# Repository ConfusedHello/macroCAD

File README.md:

# MacroCAD
My own macropad made for CAD! Made for Hackclub's Highway/Hackpad event.

</img>

For this macropad, there is a function row at the bottom to switch "layers", ie. extra buttons!!

## The PCB
The PCB was designed entirely in KiCad. Here's an image of the schematic.

And an image of the PCB!

</img>

## The Case
First time using Fusion360! Went pretty well actually. Here's what we went with.

Started off by deciding on some dimensions

And moved onto creating a sketch

Then a bit more work later, the final case

Final case design (render coming soon!)

## Bill of materials
| Component                                 | Quantity | Aliexpress |
|-------------------------------------------|----------|------------|
| 2L PCB (JLCPCB with cheap shipping)       | 1        | $3.49      |
| SMD Seeed Studio XIAO RP2040              | 1        | $5.64      |
| Gateron Milky Yellows Cherry MX Switches  | 10       | ~$3.86     |
| CherryMX 1.00u Kailh Sockets              | 10       | $2.89      |
| 1N4148W Diodes (SOD-123)                  | 10       | $1.09      |
| Brass M2 Screws (approx 5mm)              | 10       | $0.97      |
| M2 Heat inserts (approx 3mm)              | 10       | $0.97      |

## Acknowledgements
- Matteo Spinelli's [Anatomy of a keyboard](https://matt3o.com/anatomy-of-a-keyboard/) for the plate thickness and hole dimensions
- MX Cherry switches footprint from [daprice/keyswitches.pretty](https://github.com/daprice/keyswitches.pretty)

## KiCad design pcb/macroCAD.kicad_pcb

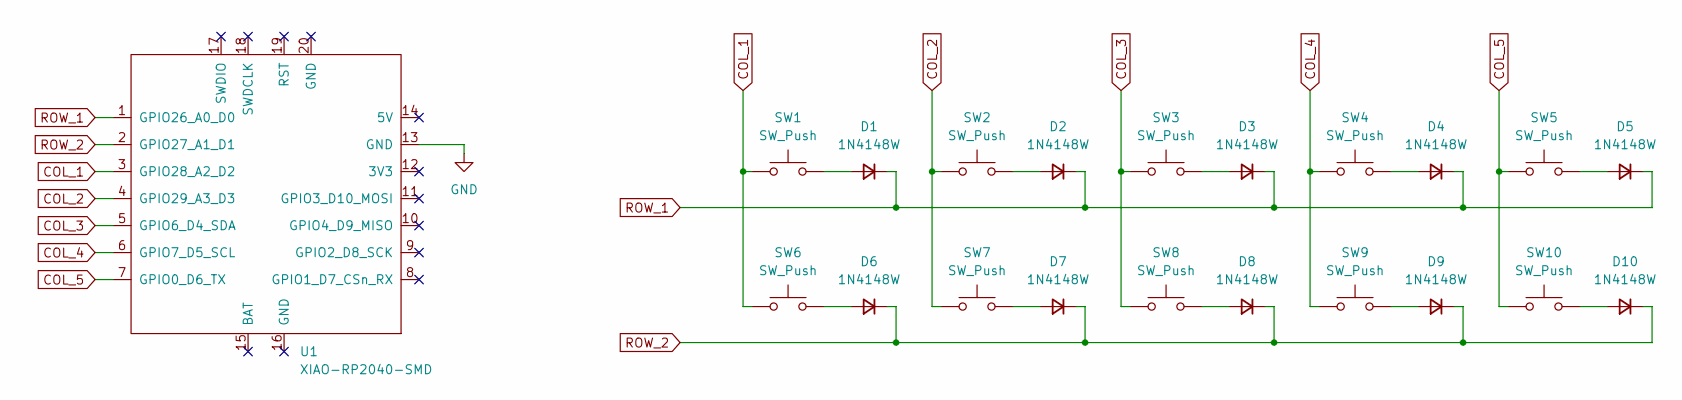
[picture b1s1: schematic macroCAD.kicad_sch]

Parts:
D1, D2, D3, D4, D5, D6, D7, D8, D9, D10: 1N4148W; D_SOD-123
SW1, SW2, SW3, SW4, SW5, SW6, SW7, SW8, SW9, SW10: SW_Push; Kailh_socket_MX
U1: XIAO-RP2040-SMD; XIAO_rp2040_SMD

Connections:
COL_1: SW1.1, SW6.1, U1.3 (GPIO28_A2_D2)
COL_2: SW2.1, SW7.1, U1.4 (GPIO29_A3_D3)
COL_3: SW3.1, SW8.1, U1.5 (GPIO6_D4_SDA)
COL_4: SW4.1, SW9.1, U1.6 (GPIO7_D5_SCL)
COL_5: SW5.1, SW10.1, U1.7 (GPIO0_D6_TX)
GND: U1.13 (GND)
unnamed: D1.2 (A), SW1.2
unnamed: D2.2 (A), SW2.2
unnamed: D3.2 (A), SW3.2
unnamed: D4.2 (A), SW4.2
unnamed: D5.2 (A), SW5.2
unnamed: D6.2 (A), SW6.2
unnamed: D7.2 (A), SW7.2
unnamed: D8.2 (A), SW8.2
unnamed: D9.2 (A), SW9.2
unnamed: D10.2 (A), SW10.2
ROW_1: D1.1 (K), D2.1 (K), D3.1 (K), D4.1 (K), D5.1 (K), U1.1 (GPIO26_A0_D0)
ROW_2: D6.1 (K), D7.1 (K), D8.1 (K), D9.1 (K), D10.1 (K), U1.2 (GPIO27_A1_D1)

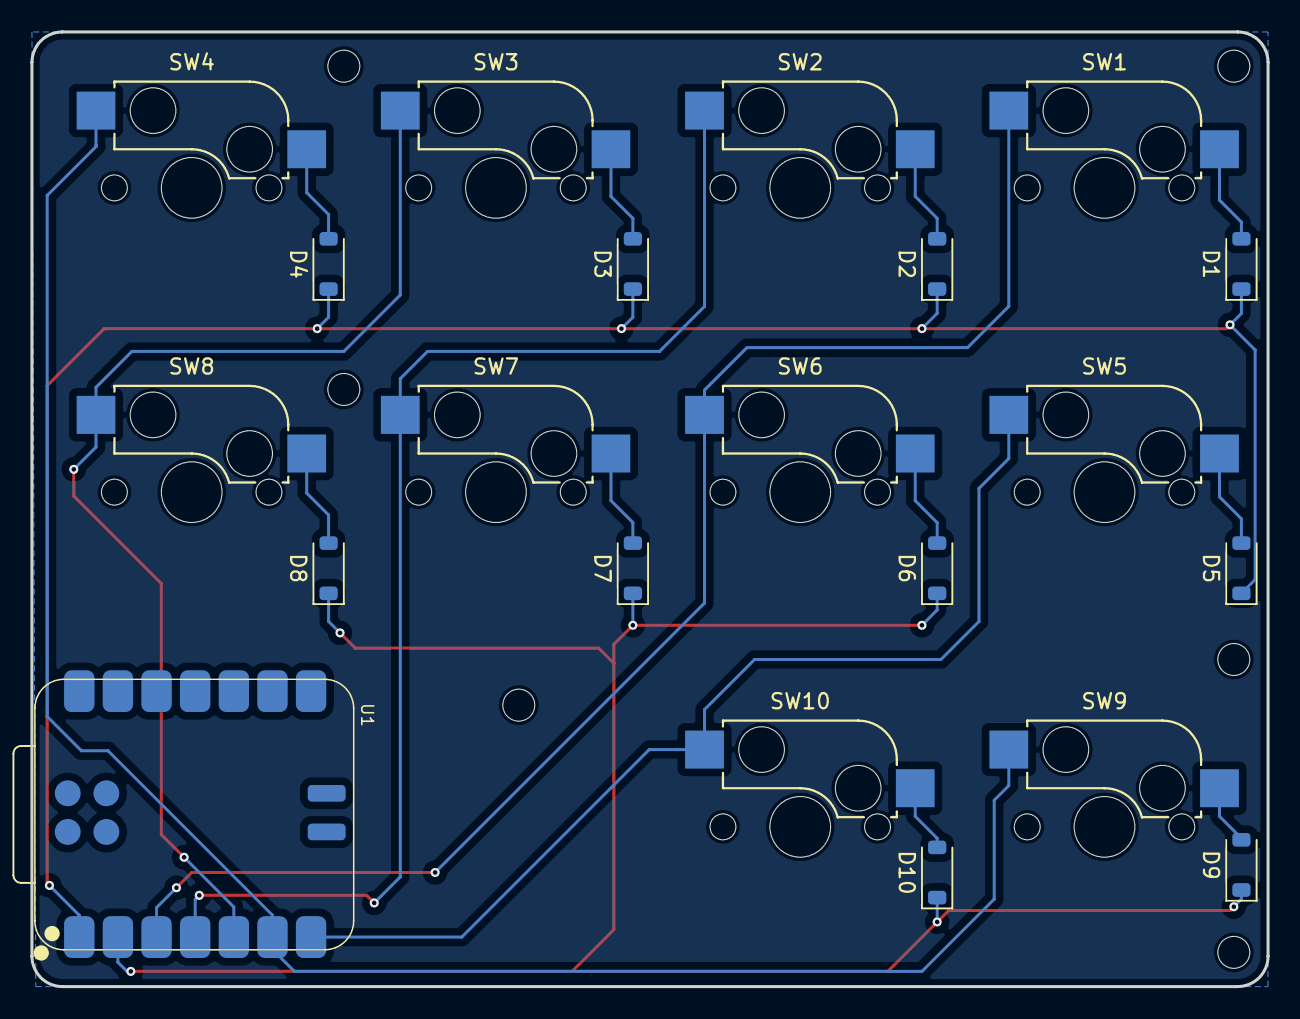
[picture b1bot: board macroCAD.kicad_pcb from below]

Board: 2 copper layers, 81.2 x 62.8 mm, 21 parts (11 on the bottom side), 17 nets.

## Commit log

2025-05-28 Add .gitignore for KiCad
2025-05-28 Upload PCB Design
2025-05-28 Add case design files
2025-05-28 Add case to README
2025-05-28 Upload KMK firmware
2025-05-28 Add GND plane to PCB
2025-05-28 Add screenshot of case
2025-05-28 Add prices to README
2025-08-15 Upload built images
